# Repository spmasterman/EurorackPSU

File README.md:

# Eurorack PSU PCB Design #

Work in progress

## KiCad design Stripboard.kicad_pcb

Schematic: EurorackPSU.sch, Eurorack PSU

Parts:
C1, C2, C3, C4, C5, C6: 3300uF; CP_Radial_D13.0mm_P5.00mm
C7, C8, C9, C10: 1uF; CP_Radial_Tantal_D4.5mm_P5.00mm
D1, D2, D3, D4, D5, D6: 1N4004; D_A-405_P7.62mm_Horizontal
J1: 12VAC; PinHeader_1x02_P2.54mm_Vertical
J2: EURO POWER HEADER; PinHeader_2x05_P2.54mm_Vertical
R1, R2: 2.4K; R_Axial_DIN0207_L6.3mm_D2.5mm_P7.62mm_Horizontal
U1: LM7812; TO-220-3_Vertical
U2: LM7912; TO-220-3_Vertical

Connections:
GNDD: C1.2, C2.1, C3.2, C4.1, C5.2, C6.1, C7.2, C8.1, C9.2, C10.1, D5.2, D6.1, J1.2, J2.3, J2.4, J2.5, J2.6, J2.7, J2.8, R1.1, R2.2, U1.2 (GND), U2.1 (GND)
unnamed: C1.1, C3.1, C5.1, C7.1, D1.1, D3.1, U1.1 (VI)
unnamed: C2.2, C4.2, C6.2, C8.2, D2.2, D4.2, U2.2 (VI)
unnamed: C9.1, D3.2, D5.1, J2.9, J2.10, R2.1, U1.3 (VO)
unnamed: C10.2, D4.1, D6.2, J2.1, J2.2, R1.2, U2.3 (VO)
unnamed: D1.2, D2.1, J1.1

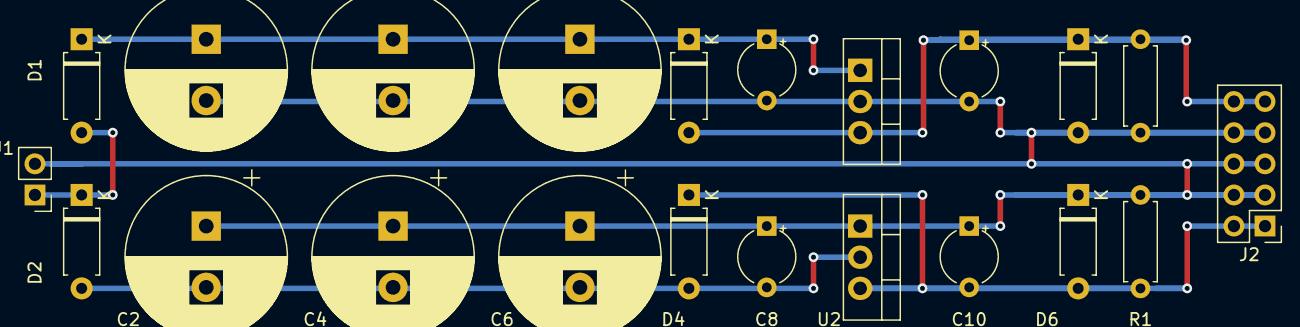
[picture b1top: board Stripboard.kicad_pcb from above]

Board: 2 copper layers, 22 parts (0 on the bottom side), 6 nets.

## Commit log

2018-08-24 Schematic
2018-08-26 stripbard layout
2018-08-26 tidy stripboard
2018-08-26 flip sides
